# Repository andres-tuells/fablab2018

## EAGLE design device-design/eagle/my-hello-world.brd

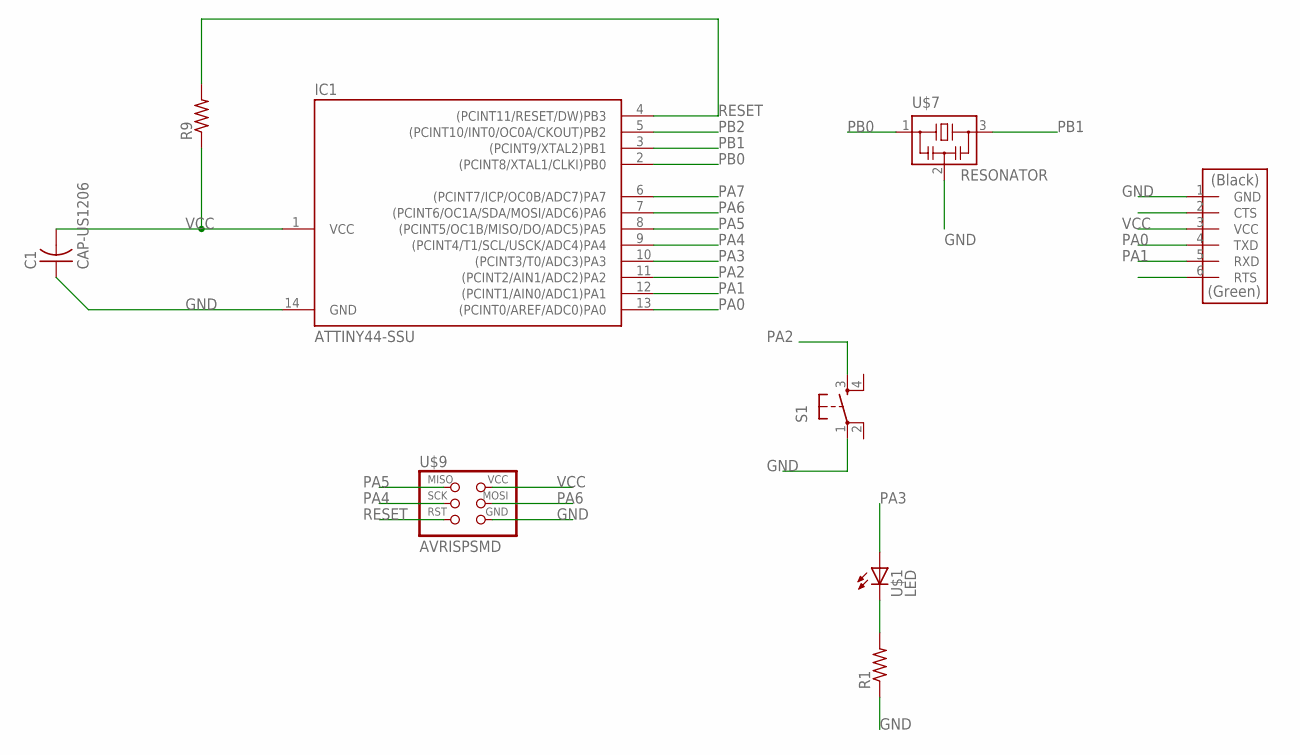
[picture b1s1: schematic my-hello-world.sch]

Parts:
C1: CAP-US1206; C1206
IC1: ATTINY44-SSU; SOIC14
R1, R9: RES-US1206; R1206
S1: 6MM_SWITCH6MM_SWITCH; 6MM_SWITCH
U$1: LED; LED1206
U$7: RESONATOR; EFOBM
U$9: AVRISPSMD; 2X03SMD
U$10: FTDI-SMD-HEADER; 1X06SMD

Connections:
GND: C1.1, IC1.14 (GND), R1.1, S1.1, U$7.2, U$9.6 (GND), U$10.1 (GND)
PA0: IC1.13 ((PCINT0/AREF/ADC0)PA0), U$10.4 (TXD)
PA1: IC1.12 ((PCINT1/AIN0/ADC1)PA1), U$10.5 (RXD)
PA2: IC1.11 ((PCINT2/AIN1/ADC2)PA2), S1.3 (S)
PA3: IC1.10 ((PCINT3/T0/ADC3)PA3), U$1.1 (A)
PA4: IC1.9 ((PCINT4/T1/SCL/USCK/ADC4)PA4), U$9.3 (SCK)
PA5: IC1.8 ((PCINT5/OC1B/MISO/DO/ADC5)PA5), U$9.1 (MISO)
PA6: IC1.7 ((PCINT6/OC1A/SDA/MOSI/ADC6)PA6), U$9.4 (MOSI)
PA7: IC1.6 ((PCINT7/ICP/OC0B/ADC7)PA7)
PB0: IC1.2 ((PCINT8/XTAL1/CLKI)PB0), U$7.1
PB1: IC1.3 ((PCINT9/XTAL2)PB1), U$7.3
PB2: IC1.5 ((PCINT10/INT0/OC0A/CKOUT)PB2)
R-LED-1: R1.2, U$1.2 (C)
RESET: IC1.4 ((PCINT11/RESET/DW)PB3), R9.2, U$9.5 (RST)
VCC: C1.2, IC1.1 (VCC), R9.1, U$9.2 (VCC), U$10.3 (VCC)

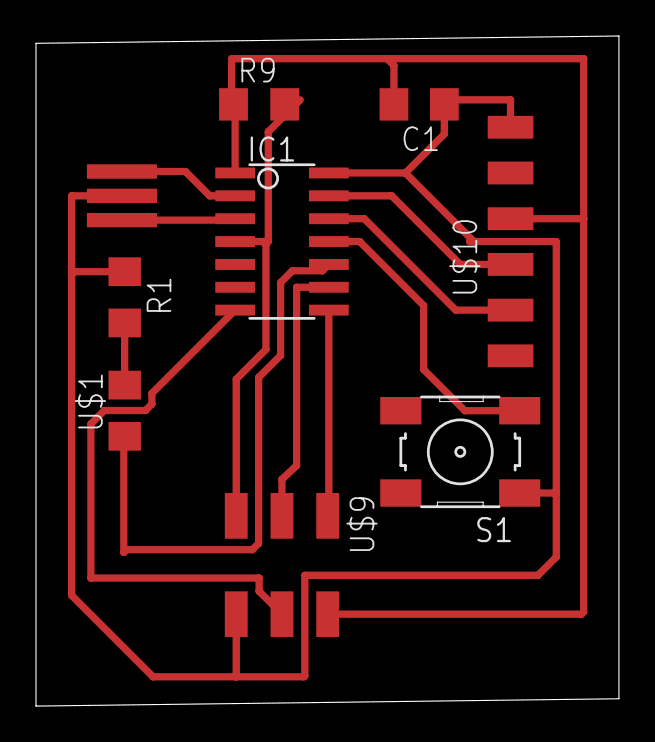
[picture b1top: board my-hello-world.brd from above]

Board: 2 copper layers, 32.4 x 37.2 mm, 9 parts (0 on the bottom side), 13 nets.

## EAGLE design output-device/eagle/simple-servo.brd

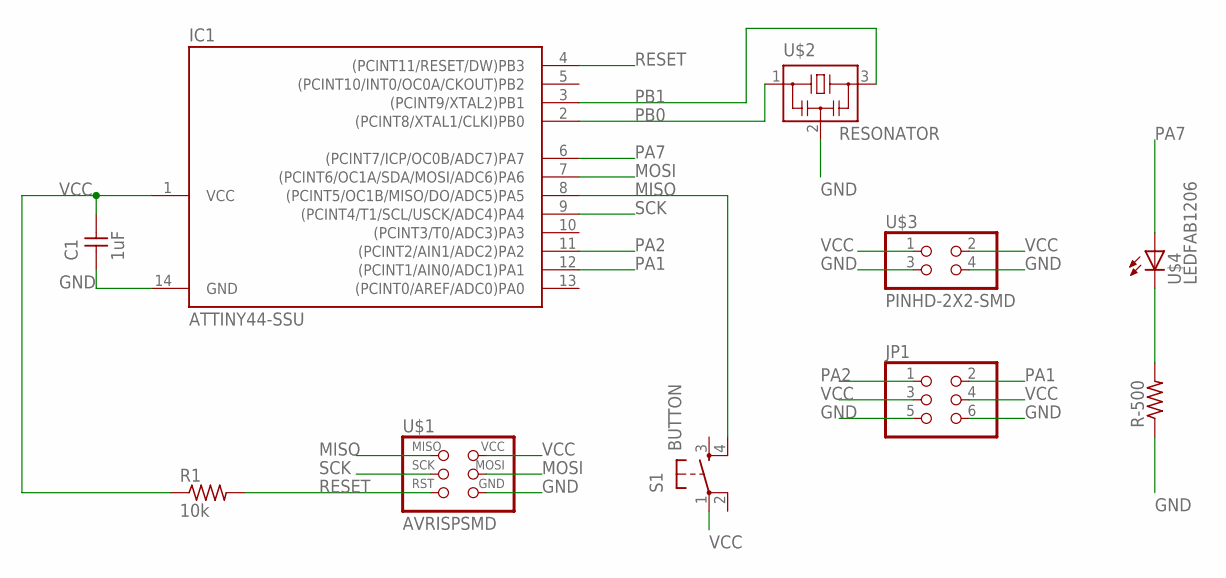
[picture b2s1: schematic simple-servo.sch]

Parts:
C1: 1uF; C1206FAB
IC1: ATTINY44-SSU; SOIC14
JP1: PINHD-2X3-SMD; 2X03SMD
R1: 10k; R1206FAB
R-500: RES-US1206FAB; R1206FAB
S1: BUTTON; 6MM_SWITCH
U$1: AVRISPSMD; 2X03SMD
U$2: RESONATOR; EFOBM
U$3: PINHD-2X2-SMD; 2X02SMD
U$4: LEDFAB1206; LED1206FAB

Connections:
GND: C1.1, IC1.14 (GND), JP1.5, JP1.6, R-500.1, U$1.6 (GND), U$2.2, U$3.3, U$3.4
MISO: IC1.8 ((PCINT5/OC1B/MISO/DO/ADC5)PA5), S1.4 (S1), U$1.1 (MISO)
MOSI: IC1.7 ((PCINT6/OC1A/SDA/MOSI/ADC6)PA6), U$1.4 (MOSI)
unnamed: R-500.2, U$4.2 (C)
PA1: IC1.12 ((PCINT1/AIN0/ADC1)PA1), JP1.2
PA2: IC1.11 ((PCINT2/AIN1/ADC2)PA2), JP1.1
PA7: IC1.6 ((PCINT7/ICP/OC0B/ADC7)PA7), U$4.1 (A)
PB0: IC1.2 ((PCINT8/XTAL1/CLKI)PB0), U$2.1
PB1: IC1.3 ((PCINT9/XTAL2)PB1), U$2.3
RESET: IC1.4 ((PCINT11/RESET/DW)PB3), R1.2, U$1.5 (RST)
SCK: IC1.9 ((PCINT4/T1/SCL/USCK/ADC4)PA4), U$1.3 (SCK)
VCC: C1.2, IC1.1 (VCC), JP1.3, JP1.4, R1.1, S1.1, U$1.2 (VCC), U$3.1, U$3.2

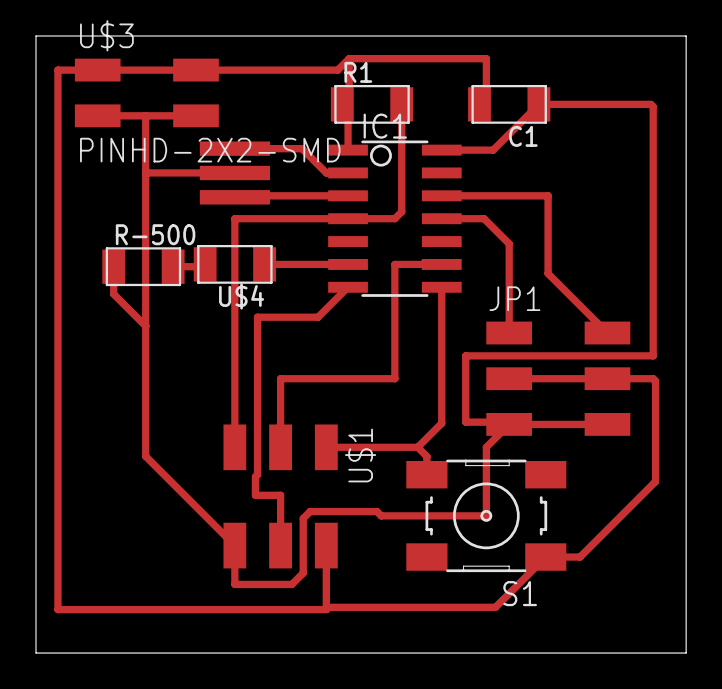
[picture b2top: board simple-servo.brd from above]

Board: 2 copper layers, 36.1 x 34.3 mm, 10 parts (0 on the bottom side), 12 nets.

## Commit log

2018-04-11 IO devices
2018-05-08 interface and application programming
